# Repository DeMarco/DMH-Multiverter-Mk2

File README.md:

# DMH-Multiverter-Mk2
Version 2 of the Multiverter module with 3 attenuverters

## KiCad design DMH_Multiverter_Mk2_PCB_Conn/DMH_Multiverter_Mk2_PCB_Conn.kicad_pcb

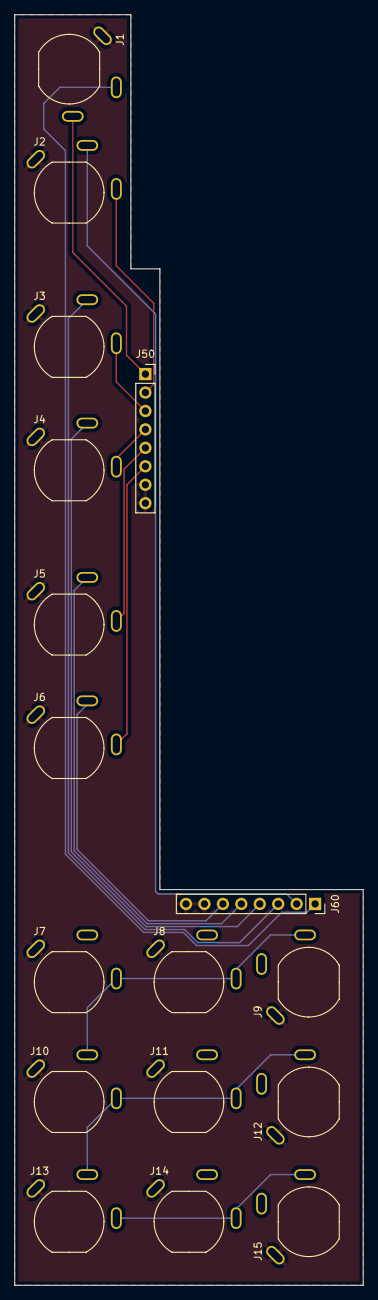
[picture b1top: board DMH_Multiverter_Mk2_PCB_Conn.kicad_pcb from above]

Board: 2 copper layers, 48.0 x 175.0 mm, 17 parts (0 on the bottom side), 16 nets.

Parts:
J1, J2, J3, J4, J5, J6, J7, J8, J9, J10, J11, J12, J13, J14, J15: TS_Jack_6.35mm_Sw; CUI_MJ-63052A
J50, J60: Conn_01x08; PinSocket_1x08_P2.54mm_Vertical

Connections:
/Inputs and Outputs/Att A Input Jack: J1.T, J50.1
/Inputs and Outputs/Att A Output Jack: J2.T, J50.2
/Inputs and Outputs/Att B Input Jack: J3.T, J50.3
/Inputs and Outputs/Att B Output Jack: J4.T, J50.4
/Inputs and Outputs/Att C Input Jack: J5.T, J50.5
/Inputs and Outputs/Att C Output Jack: J6.T, J50.6
GND: J1.S, J2.S, J3.S, J4.S, J5.S, J6.S, J7.S, J8.S, J9.S, J10.S, J11.S, J12.S, J13.S, J14.S, J15.S, J50.7, J50.8, J60.7, J60.8
unnamed: J10.T, J11.T, J12.T, J13.TN
unnamed: J7.T, J8.T, J9.T, J10.TN
unnamed: J13.T, J14.T, J15.T
unnamed: J1.TN, J60.1
unnamed: J2.TN, J60.2
unnamed: J3.TN, J60.3
unnamed: J4.TN, J60.4
unnamed: J5.TN, J60.5
unnamed: J6.TN, J60.6

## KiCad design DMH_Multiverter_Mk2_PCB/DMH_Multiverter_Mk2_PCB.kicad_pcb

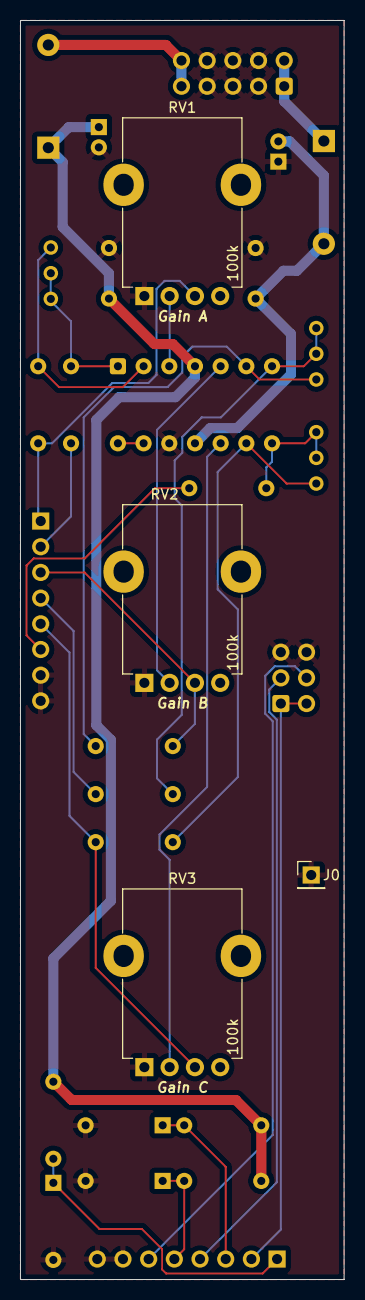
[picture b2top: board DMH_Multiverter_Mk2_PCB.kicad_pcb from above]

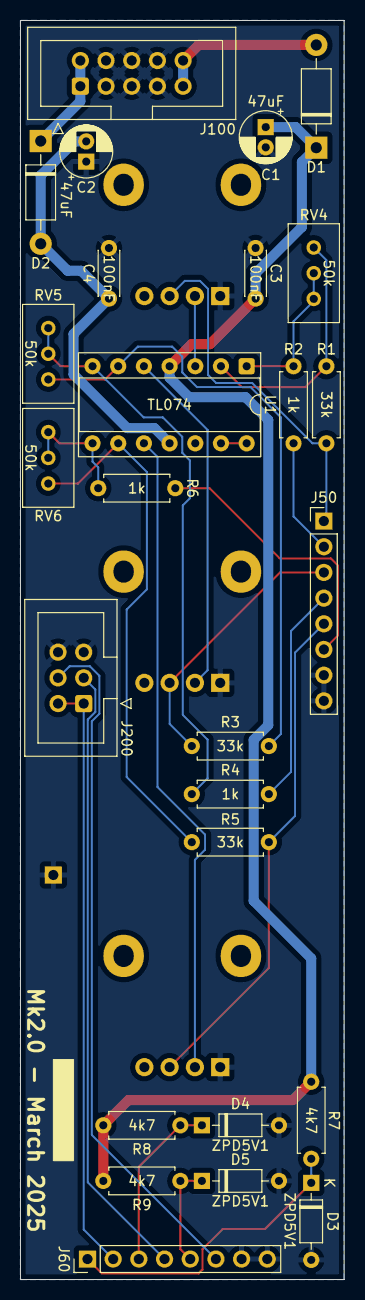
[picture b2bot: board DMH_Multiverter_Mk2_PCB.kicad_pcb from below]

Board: 2 copper layers, 32.0 x 124.5 mm, 30 parts (26 on the bottom side), 27 nets.

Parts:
C1, C2: 47uF; CP_Radial_D5.0mm_P2.00mm
C3, C4: 100nF; C_Disc_D4.3mm_W1.9mm_P5.00mm
D1: SB140+; D_DO-41_SOD81_P10.16mm_Horizontal
D2: SB140-; D_DO-41_SOD81_P10.16mm_Horizontal
D3, D4, D5: ZPD5V1; D_DO-35_SOD27_P7.62mm_Horizontal
J0: Conn_01x01; PinHeader_1x01_P2.54mm_Vertical
J50, J60: Conn_01x08; PinHeader_1x08_P2.54mm_Vertical
J100: IDC_02x05; IDC-Header_2x05_P2.54mm_Vertical_Eurorack
J200: BackBone_Connector_6pin; IDC-Header_2x03_P2.54mm_Vertical_BackBone
R1, R3, R5: 33k; R_Axial_DIN0207_L6.3mm_D2.5mm_P7.62mm_Horizontal
R2, R4, R6: 1k; R_Axial_DIN0207_L6.3mm_D2.5mm_P7.62mm_Horizontal
R7, R8, R9: 4k7; R_Axial_DIN0207_L6.3mm_D2.5mm_P7.62mm_Horizontal
RV1, RV2, RV3: 100k; Potentiometer_TT_P110KH1
RV4, RV5, RV6: 50k; Potentiometer_Bourns_3296W_Vertical
U1: TL074; DIP-14_W7.62mm_Socket

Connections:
+12V: C1.1, C3.1, D1.1 (K), R7.2, R8.2, R9.2, U1.4 (V+)
-12V: C2.2, C4.2, D2.2 (A), U1.11 (V-)
/Core Circuit/Att A Input: J50.1, R1.1, RV1.3
/Core Circuit/Att A Output: J50.2, R2.2
/Core Circuit/Att B Input: J50.3, R3.1, RV2.3
/Core Circuit/Att B Output: J50.4, R4.2
/Core Circuit/Att C Input: J50.5, R5.1, RV3.3
/Core Circuit/Att C Output: J50.6, R6.2
GND: C1.2, C2.1, C3.2, C4.1, D3.2 (A), D4.2 (A), D5.2 (A), J0.1, J50.7, J50.8, J60.7, J60.8, J100.2a, J100.2b, J100.3a, J100.3b, J100.4a, J100.4b, J200.3, J200.6, RV1.1, RV2.1, RV3.1, U1.12 (+)
unnamed: D1.2 (A), J100.5a, J100.5b
unnamed: D2.1 (K), J100.1a, J100.1b
unnamed: D3.1 (K), J60.1, R7.1
unnamed: D4.1 (K), J60.3, R8.1
unnamed: D5.1 (K), J60.5, R9.1
unnamed: J60.2, J200.1, J200.4
unnamed: J60.4, J200.2
unnamed: J60.6, J200.5
unnamed: R2.1, RV4.2, RV4.3, U1.1
unnamed: R4.1, RV5.2, RV5.3, U1.7
unnamed: R6.1, RV6.2, RV6.3, U1.8
unnamed: RV1.2, U1.3 (+)
unnamed: R1.2, RV4.1, U1.2 (-)
unnamed: RV2.2, U1.5 (+)
unnamed: R3.2, RV5.1, U1.6 (-)
unnamed: RV3.2, U1.10 (+)
unnamed: R5.2, RV6.1, U1.9 (-)
unnamed: U1.13 (-), U1.14

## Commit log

2025-03-01 Copied Mk1 projects
2025-03-01 Added 3rd attenuverter to Panel and Schematic
2025-03-01 Main PCB update ongoing
2025-03-01 Main PCB components placed
2025-03-01 Routed main PCB
2025-03-01 pcb 2 in progress
2025-03-02 Routed Connectors PCB
2025-03-09 Independent zeners for normalled 5V DC offset
2025-03-15 Generated Gerbers
2025-05-07 Exported BoM
2025-08-01 Uploaded BoM
2025-12-06 KiCad 9
